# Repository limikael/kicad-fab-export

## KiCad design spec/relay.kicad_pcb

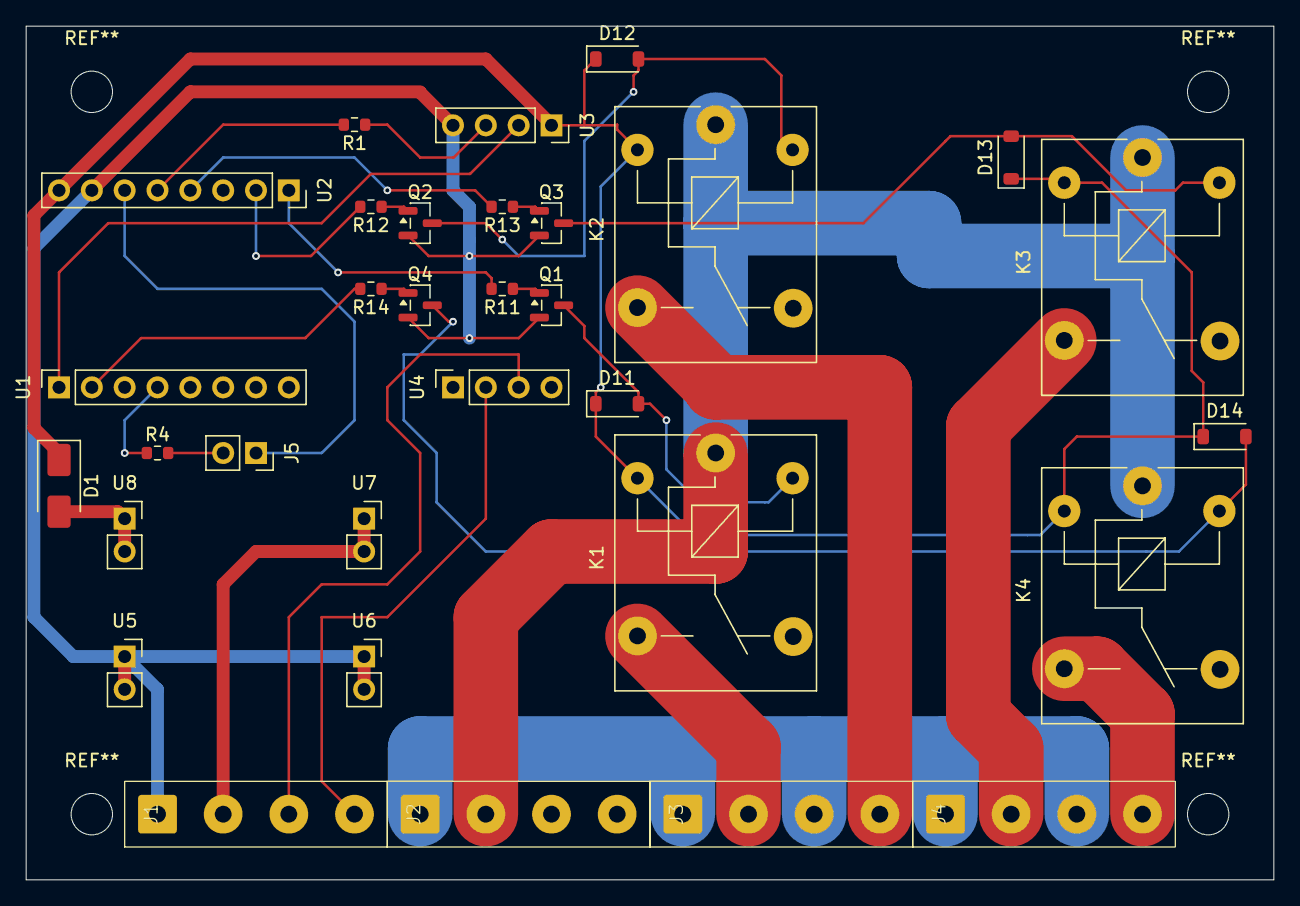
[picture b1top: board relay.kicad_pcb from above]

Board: 2 copper layers, 96.5 x 66.0 mm, 32 parts (0 on the bottom side), 30 nets.

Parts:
D1: D_SMA
D11, D12, D13, D14: D_SOD-123
J1, J2, J3, J4: ScrewTerminals_4P
J5: PinSocket_1x02_P2.54mm_Vertical
K1, K2, K3, K4: Relay_SPDT_SANYOU_SRD_Series_Form_C
Q1, Q2, Q3, Q4: SOT-23
R1: 4.7k; R_0603_1608Metric
R4: 330; R_0603_1608Metric
R11, R12, R13, R14: 1k; R_0603_1608Metric
U1, U2: PinSocket_1x08_P2.54mm_Vertical
U3, U4: PinSocket_1x04_P2.54mm_Vertical
U5, U6, U7, U8: PinSocket_1x02_P2.54mm_Vertical

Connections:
/3V3: J5.1, U2.6
/5V: D1.1 (K), D11.1 (K), D12.1 (K), D13.1 (K), D14.1 (K), K1.2, K2.2, K3.2, K4.2, U2.8, U3.1
/12V: J1.2, U7.1, U7.2
/ACL: J2.2, K1.1, K2.1, K3.1, K4.1
/ACN: J2.1, J3.1, J3.3, J4.1, J4.3
/CANH: J1.3, U4.3
/CANL: J1.4, U4.2
/GND: J1.1, Q1.2 (E), Q2.2 (E), Q3.2 (E), Q4.2 (E), U2.7, U3.4, U5.1, U5.2, U6.1, U6.2
unnamed: D1.2 (A), U8.1, U8.2
unnamed: D11.2 (A), K1.5, Q1.3 (C)
unnamed: D12.2 (A), K2.5, Q2.3 (C)
unnamed: D13.2 (A), K3.5, Q3.3 (C)
unnamed: D14.2 (A), K4.5, Q4.3 (C)
unnamed: J3.2, K1.3
unnamed: J3.4, K2.3
unnamed: J4.2, K3.3
unnamed: J4.4, K4.3
unnamed: J5.2, R4.2
unnamed: Q1.1 (B), R11.1
unnamed: Q2.1 (B), R12.1
unnamed: Q3.1 (B), R13.1
unnamed: Q4.1 (B), R14.1
unnamed: U1.1, U3.2
unnamed: R14.2, U1.2
unnamed: R4.1, U1.4
unnamed: R11.2, U2.1
unnamed: R12.2, U2.2
unnamed: R13.2, U2.4
unnamed: R1.2, U2.5
unnamed: R1.1, U3.3

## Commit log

2026-06-05 browser automation
2026-06-05 correct project name
2026-06-05 tmp dir
2026-06-05 clean out existing
2026-06-19 more roboust browser automation
